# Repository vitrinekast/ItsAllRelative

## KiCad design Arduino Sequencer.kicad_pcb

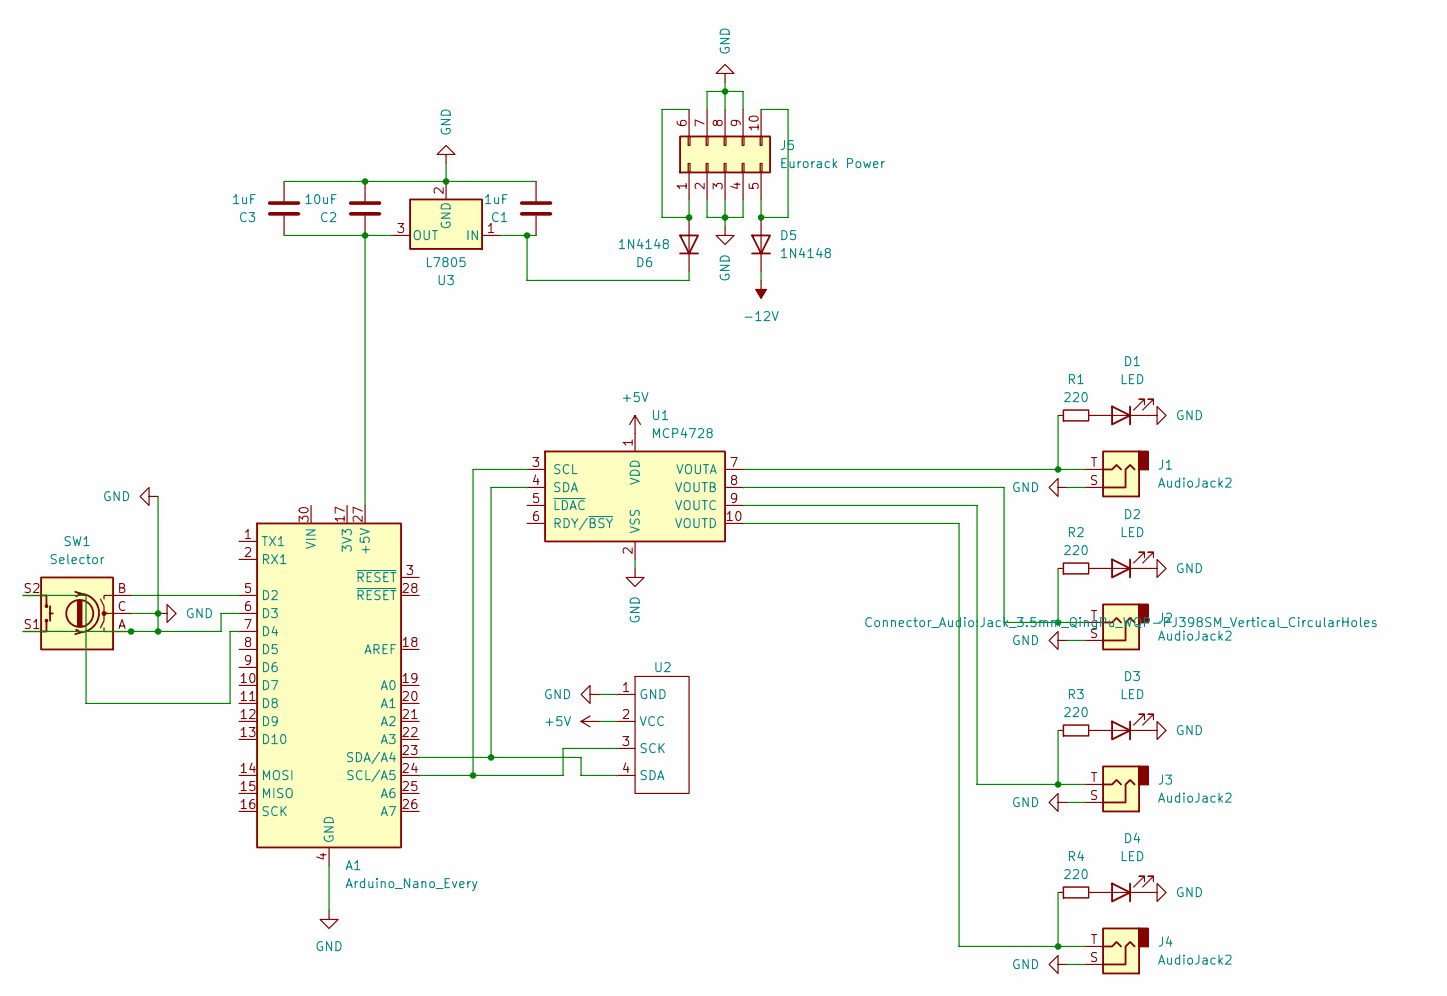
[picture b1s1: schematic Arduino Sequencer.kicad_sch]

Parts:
A1: Arduino_Nano_Every; Arduino_Nano
C1, C3: 1uF; CP_Radial_D6.3mm_P2.50mm
C2: 10uF; CP_Radial_D6.3mm_P2.50mm
D1, D2, D3, D4: LED; LED_D4.0mm
D5, D6: 1N4148; D_DO-27_P5.08mm_Vertical_AnodeUp
J1, J2, J3, J4: AudioJack2; Jack_3.5mm_QingPu_WQP-PJ398SM_Vertical_CircularHoles
J5: Eurorack Power; PinHeader_2x05_P1.00mm_Vertical
R1, R2, R3, R4: 220; R_Box_L13.0mm_W4.0mm_P9.00mm
SW1: Selector; RotaryEncoder_Alps_EC11E-Switch_Vertical_H20mm
U1: MCP4728; MSOP-10_3x3mm_P0.5mm
U2: (no value)
U3: L7805

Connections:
+5V: U1.1 (VDD), U2.2 (VCC)
-12V: D5.1 (K)
GND: A1.4 (GND), A1.6 (D3), A1.29 (GND), C1.2, C2.1, C3.1, D1.1 (K), D2.1 (K), D3.1 (K), D4.1 (K), J1.S, J2.S, J3.S, J4.S, J5.2, J5.3, J5.4, J5.7, J5.8, J5.9, SW1.A, SW1.C, SW1.S1, U1.2 (VSS), U2.1 (GND), U3.2 (GND)
unnamed: A1.27 (+5V), C2.2, C3.2, U3.3 (OUT)
unnamed: A1.5 (D2), SW1.B
unnamed: A1.7 (D4), SW1.S2
unnamed: A1.24 (SCL/A5), U1.3 (SCL), U2.3 (SCK)
unnamed: A1.23 (SDA/A4), U1.4 (SDA), U2.4 (SDA)
unnamed: D1.2 (A), R1.2
unnamed: D2.2 (A), R2.2
unnamed: D3.2 (A), R3.2
unnamed: D4.2 (A), R4.2
unnamed: D5.2 (A), J5.5, J5.10
unnamed: D6.2 (A), J5.1, J5.6
unnamed: C1.1, D6.1 (K), U3.1 (IN)
unnamed: J1.T, R1.1, U1.7 (VOUTA)
unnamed: J2.T, R2.1, U1.8 (VOUTB)
unnamed: J3.T, R3.1, U1.9 (VOUTC)
unnamed: J4.T, R4.1, U1.10 (VOUTD)

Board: 2 copper layers, 21 parts (0 on the bottom side), 17 nets, no tracks yet.

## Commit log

2024-07-03 init commit
2024-07-03 move gitignore
2024-07-05 include schematic
2024-07-16 replace display library
2024-07-17 change dac address
2024-07-17 simplify make file
2024-07-18 include new modifiers
